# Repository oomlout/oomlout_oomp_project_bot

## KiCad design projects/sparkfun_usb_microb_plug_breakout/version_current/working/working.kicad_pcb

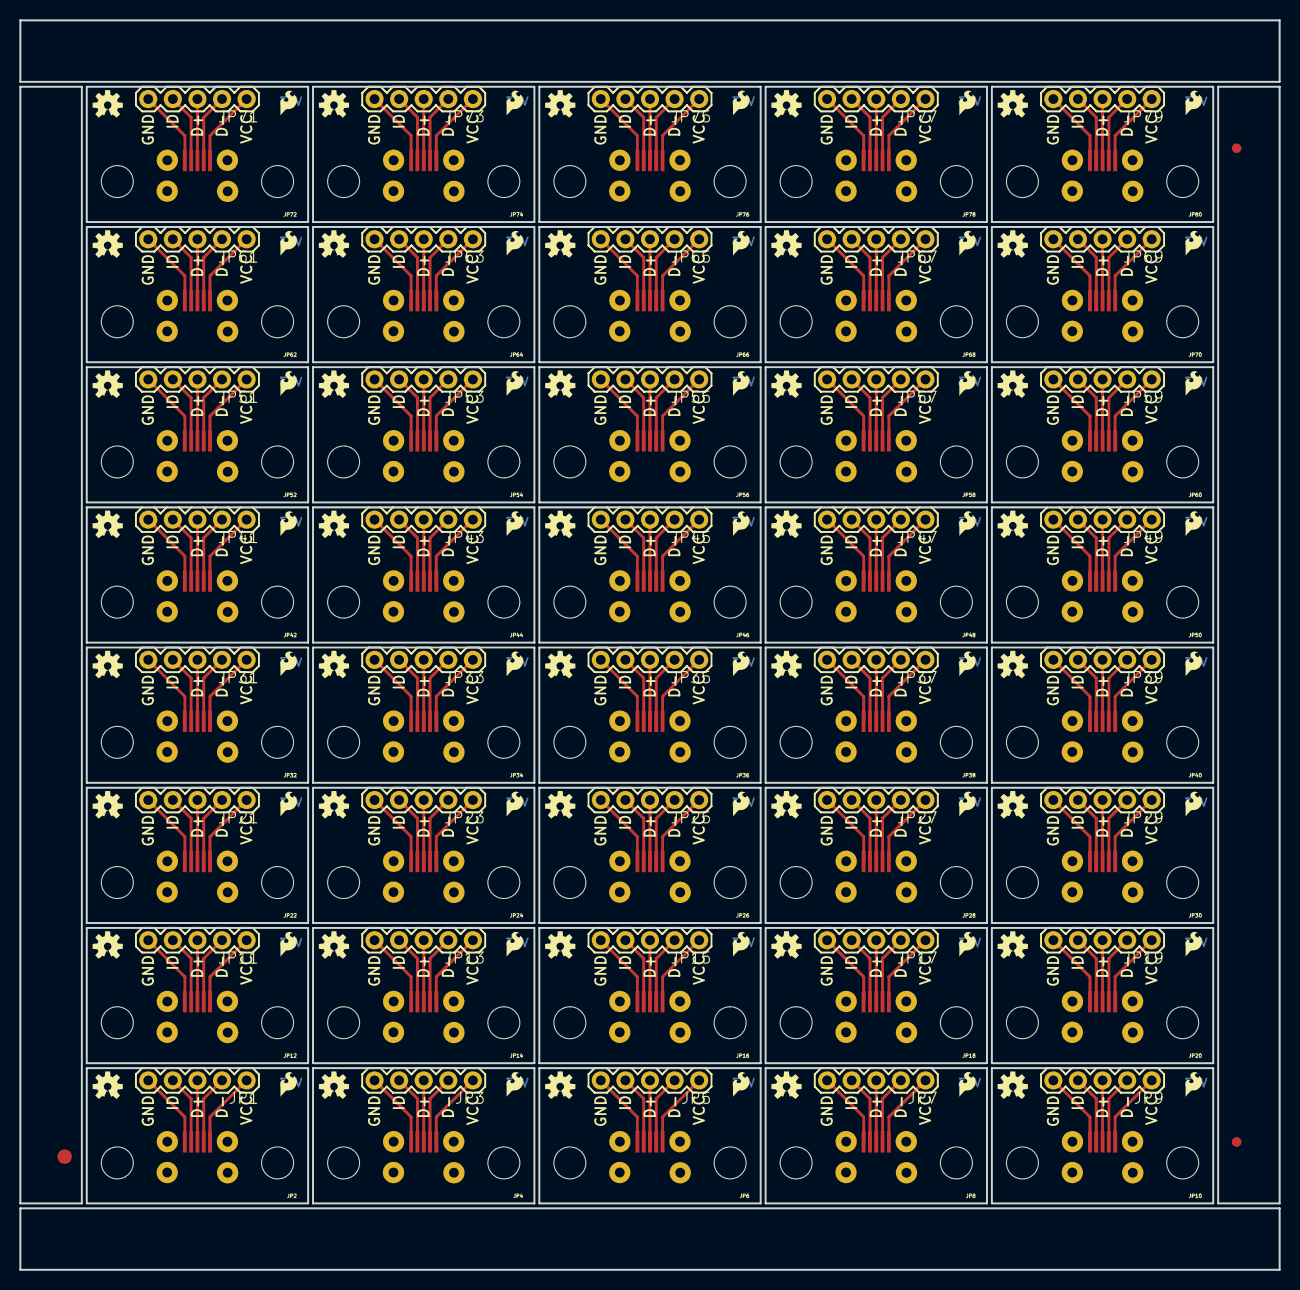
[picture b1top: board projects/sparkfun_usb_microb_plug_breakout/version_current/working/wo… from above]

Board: 2 copper layers, 130.0 x 129.0 mm, 163 parts (0 on the bottom side), 200 nets.

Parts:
E$1: FIDUCIAL-1.5X3
E$4, E$5: FIDUCIAL-1X2
JP1, JP3, JP5, JP7, JP9, JP11, JP13, JP15, JP17, JP19, JP21, JP23, JP25, JP27, JP29, JP31, JP33, JP35, JP37, JP39, JP41, JP43, JP45, JP47, JP49, JP51, JP53, JP55, JP57, JP59, JP61, JP63, JP65, JP67, JP69, JP71, JP73, JP75, JP77, JP79: 1X05
JP2, JP4, JP6, JP8, JP10, JP12, JP14, JP16, JP18, JP20, JP22, JP24, JP26, JP28, JP30, JP32, JP34, JP36, JP38, JP40, JP42, JP44, JP46, JP48, JP50, JP52, JP54, JP56, JP58, JP60, JP62, JP64, JP66, JP68, JP70, JP72, JP74, JP76, JP78, JP80: USB Micro B Plug; MICRO-B-SMT
LOGO1, LOGO3, LOGO5, LOGO7, LOGO9, LOGO11, LOGO13, LOGO15, LOGO17, LOGO19, LOGO21, LOGO23, LOGO25, LOGO27, LOGO29, LOGO31, LOGO33, LOGO35, LOGO37, LOGO39, LOGO41, LOGO43, LOGO45, LOGO47, LOGO49, LOGO51, LOGO53, LOGO55, LOGO57, LOGO59, LOGO61, LOGO63, LOGO65, LOGO67, LOGO69, LOGO71, LOGO73, LOGO75, LOGO77, LOGO79: OSHW-LOGOS; OSHW-LOGO-S
LOGO2, LOGO4, LOGO6, LOGO8, LOGO10, LOGO12, LOGO14, LOGO16, LOGO18, LOGO20, LOGO22, LOGO24, LOGO26, LOGO28, LOGO30, LOGO32, LOGO34, LOGO36, LOGO38, LOGO40, LOGO42, LOGO44, LOGO46, LOGO48, LOGO50, LOGO52, LOGO54, LOGO56, LOGO58, LOGO60, LOGO62, LOGO64, LOGO66, LOGO68, LOGO70, LOGO72, LOGO74, LOGO76, LOGO78, LOGO80: SFE_LOGO_FLAME.1_INCH; SFE_LOGO_FLAME_.1

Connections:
unnamed: JP1.1, JP2.1
unnamed: JP1.2, JP2.2
unnamed: JP1.3, JP2.3
unnamed: JP1.4, JP2.4
unnamed: JP1.5, JP2.5
unnamed: JP3.1, JP4.1
unnamed: JP3.2, JP4.2
unnamed: JP3.3, JP4.3
unnamed: JP3.4, JP4.4
unnamed: JP3.5, JP4.5
unnamed: JP5.1, JP6.1
unnamed: JP5.2, JP6.2
unnamed: JP5.3, JP6.3
unnamed: JP5.4, JP6.4
unnamed: JP5.5, JP6.5
unnamed: JP7.1, JP8.1
unnamed: JP7.2, JP8.2
unnamed: JP7.3, JP8.3
unnamed: JP7.4, JP8.4
unnamed: JP7.5, JP8.5
unnamed: JP9.1, JP10.1
unnamed: JP9.2, JP10.2
unnamed: JP9.3, JP10.3
unnamed: JP9.4, JP10.4
unnamed: JP9.5, JP10.5
unnamed: JP11.1, JP12.1
unnamed: JP11.2, JP12.2
unnamed: JP11.3, JP12.3
unnamed: JP11.4, JP12.4
unnamed: JP11.5, JP12.5
unnamed: JP13.1, JP14.1
unnamed: JP13.2, JP14.2
unnamed: JP13.3, JP14.3
unnamed: JP13.4, JP14.4
unnamed: JP13.5, JP14.5
unnamed: JP15.1, JP16.1
unnamed: JP15.2, JP16.2
unnamed: JP15.3, JP16.3
unnamed: JP15.4, JP16.4
unnamed: JP15.5, JP16.5
unnamed: JP17.1, JP18.1
unnamed: JP17.2, JP18.2
unnamed: JP17.3, JP18.3
unnamed: JP17.4, JP18.4
unnamed: JP17.5, JP18.5
unnamed: JP19.1, JP20.1
unnamed: JP19.2, JP20.2
unnamed: JP19.3, JP20.3
unnamed: JP19.4, JP20.4
unnamed: JP19.5, JP20.5
unnamed: JP21.1, JP22.1
unnamed: JP21.2, JP22.2
unnamed: JP21.3, JP22.3
unnamed: JP21.4, JP22.4
unnamed: JP21.5, JP22.5
unnamed: JP23.1, JP24.1
unnamed: JP23.2, JP24.2
unnamed: JP23.3, JP24.3
unnamed: JP23.4, JP24.4
unnamed: JP23.5, JP24.5
unnamed: JP25.1, JP26.1
unnamed: JP25.2, JP26.2
unnamed: JP25.3, JP26.3
unnamed: JP25.4, JP26.4
unnamed: JP25.5, JP26.5
unnamed: JP27.1, JP28.1
unnamed: JP27.2, JP28.2
unnamed: JP27.3, JP28.3
unnamed: JP27.4, JP28.4
unnamed: JP27.5, JP28.5
unnamed: JP29.1, JP30.1
unnamed: JP29.2, JP30.2
unnamed: JP29.3, JP30.3
unnamed: JP29.4, JP30.4
unnamed: JP29.5, JP30.5
unnamed: JP31.1, JP32.1
unnamed: JP31.2, JP32.2
unnamed: JP31.3, JP32.3
unnamed: JP31.4, JP32.4
unnamed: JP31.5, JP32.5
unnamed: JP33.1, JP34.1
unnamed: JP33.2, JP34.2
unnamed: JP33.3, JP34.3
unnamed: JP33.4, JP34.4
unnamed: JP33.5, JP34.5
unnamed: JP35.1, JP36.1
unnamed: JP35.2, JP36.2
unnamed: JP35.3, JP36.3
unnamed: JP35.4, JP36.4
unnamed: JP35.5, JP36.5
unnamed: JP37.1, JP38.1
unnamed: JP37.2, JP38.2
unnamed: JP37.3, JP38.3
unnamed: JP37.4, JP38.4
unnamed: JP37.5, JP38.5
unnamed: JP39.1, JP40.1
unnamed: JP39.2, JP40.2
unnamed: JP39.3, JP40.3
unnamed: JP39.4, JP40.4
unnamed: JP39.5, JP40.5
unnamed: JP41.1, JP42.1
unnamed: JP41.2, JP42.2
unnamed: JP41.3, JP42.3
unnamed: JP41.4, JP42.4
unnamed: JP41.5, JP42.5
unnamed: JP43.1, JP44.1
unnamed: JP43.2, JP44.2
unnamed: JP43.3, JP44.3
unnamed: JP43.4, JP44.4
unnamed: JP43.5, JP44.5
unnamed: JP45.1, JP46.1
unnamed: JP45.2, JP46.2
unnamed: JP45.3, JP46.3
unnamed: JP45.4, JP46.4
unnamed: JP45.5, JP46.5
unnamed: JP47.1, JP48.1
unnamed: JP47.2, JP48.2
unnamed: JP47.3, JP48.3
unnamed: JP47.4, JP48.4
unnamed: JP47.5, JP48.5
unnamed: JP49.1, JP50.1
unnamed: JP49.2, JP50.2
unnamed: JP49.3, JP50.3
unnamed: JP49.4, JP50.4
unnamed: JP49.5, JP50.5
unnamed: JP51.1, JP52.1
unnamed: JP51.2, JP52.2
unnamed: JP51.3, JP52.3
unnamed: JP51.4, JP52.4
unnamed: JP51.5, JP52.5
unnamed: JP53.1, JP54.1
unnamed: JP53.2, JP54.2
unnamed: JP53.3, JP54.3
unnamed: JP53.4, JP54.4
unnamed: JP53.5, JP54.5
unnamed: JP55.1, JP56.1
unnamed: JP55.2, JP56.2
unnamed: JP55.3, JP56.3
unnamed: JP55.4, JP56.4
unnamed: JP55.5, JP56.5
unnamed: JP57.1, JP58.1
unnamed: JP57.2, JP58.2
unnamed: JP57.3, JP58.3
unnamed: JP57.4, JP58.4
unnamed: JP57.5, JP58.5
unnamed: JP59.1, JP60.1
unnamed: JP59.2, JP60.2
unnamed: JP59.3, JP60.3
unnamed: JP59.4, JP60.4
unnamed: JP59.5, JP60.5
unnamed: JP61.1, JP62.1
unnamed: JP61.2, JP62.2
unnamed: JP61.3, JP62.3
unnamed: JP61.4, JP62.4
unnamed: JP61.5, JP62.5
unnamed: JP63.1, JP64.1
unnamed: JP63.2, JP64.2
unnamed: JP63.3, JP64.3
unnamed: JP63.4, JP64.4
unnamed: JP63.5, JP64.5
unnamed: JP65.1, JP66.1
unnamed: JP65.2, JP66.2
unnamed: JP65.3, JP66.3
unnamed: JP65.4, JP66.4
unnamed: JP65.5, JP66.5
unnamed: JP67.1, JP68.1
unnamed: JP67.2, JP68.2
unnamed: JP67.3, JP68.3
unnamed: JP67.4, JP68.4
unnamed: JP67.5, JP68.5
unnamed: JP69.1, JP70.1
unnamed: JP69.2, JP70.2
unnamed: JP69.3, JP70.3
unnamed: JP69.4, JP70.4
unnamed: JP69.5, JP70.5
unnamed: JP71.1, JP72.1
unnamed: JP71.2, JP72.2
unnamed: JP71.3, JP72.3
unnamed: JP71.4, JP72.4
unnamed: JP71.5, JP72.5
unnamed: JP73.1, JP74.1
unnamed: JP73.2, JP74.2
unnamed: JP73.3, JP74.3
unnamed: JP73.4, JP74.4
unnamed: JP73.5, JP74.5
unnamed: JP75.1, JP76.1
unnamed: JP75.2, JP76.2
unnamed: JP75.3, JP76.3
unnamed: JP75.4, JP76.4
unnamed: JP75.5, JP76.5
unnamed: JP77.1, JP78.1
unnamed: JP77.2, JP78.2
unnamed: JP77.3, JP78.3
unnamed: JP77.4, JP78.4
unnamed: JP77.5, JP78.5
unnamed: JP79.1, JP80.1
unnamed: JP79.2, JP80.2
unnamed: JP79.3, JP80.3
unnamed: JP79.4, JP80.4
unnamed: JP79.5, JP80.5

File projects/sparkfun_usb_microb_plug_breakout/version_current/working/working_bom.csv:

"Id";"Designator";"Footprint";"Quantity";"Designation";"Supplier and ref";
1;"LOGO5,LOGO25,LOGO69,LOGO53,LOGO77,LOGO17,LOGO79,LOGO11,LOGO43,LOGO55,LOGO71,LOGO61,LOGO13,LOGO33,LOGO21,LOGO3,LOGO63,LOGO15,LOGO35,LOGO45,LOGO41,LOGO9,LOGO59,LOGO51,LOGO49,LOGO67,LOGO73,LOGO47,LOGO19,LOGO57,LOGO39,LOGO7,LOGO29,LOGO23,LOGO75,LOGO37,LOGO1,LOGO27,LOGO31,LOGO65";"OSHW-LOGO-S";40;"OSHW-LOGOS";;;
2;"LOGO74,LOGO68,LOGO24,LOGO14,LOGO76,LOGO46,LOGO54,LOGO42,LOGO30,LOGO50,LOGO38,LOGO64,LOGO62,LOGO12,LOGO70,LOGO60,LOGO48,LOGO36,LOGO22,LOGO78,LOGO16,LOGO52,LOGO2,LOGO6,LOGO80,LOGO32,LOGO18,LOGO8,LOGO56,LOGO72,LOGO66,LOGO28,LOGO40,LOGO44,LOGO10,LOGO20,LOGO4,LOGO58,LOGO34,LOGO26";"SFE_LOGO_FLAME_.1";40;"SFE_LOGO_FLAME.1_INCH";;;
3;"JP75,JP55,JP21,JP9,JP65,JP59,JP79,JP19,JP25,JP51,JP29,JP57,JP31,JP39,JP7,JP35,JP69,JP49,JP41,JP73,JP67,JP33,JP15,JP53,JP27,JP5,JP13,JP43,JP3,JP11,JP63,JP17,JP1,JP37,JP45,JP47,JP71,JP77,JP23,JP61";"1X05";40;"";;;
4;"JP68,JP64,JP50,JP72,JP54,JP58,JP36,JP14,JP16,JP38,JP20,JP24,JP4,JP46,JP48,JP56,JP40,JP2,JP30,JP26,JP52,JP44,JP22,JP18,JP10,JP66,JP76,JP8,JP12,JP60,JP34,JP70,JP28,JP6,JP62,JP32,JP78,JP74,JP42,JP80";"MICRO-B-SMT";40;"USB Micro B Plug";;;
5;"E$4,E$5";"FIDUCIAL-1X2";2;"";;;
6;"E$1";"FIDUCIAL-1.5X3";1;"";;;

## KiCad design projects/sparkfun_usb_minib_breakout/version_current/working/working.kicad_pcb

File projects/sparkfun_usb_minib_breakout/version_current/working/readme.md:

# USB_miniB_Breakout by sparkfun  
This is a harvested standardized copy of a project from github.  
The original project can be found at:  
https://github.com/sparkfun/USB_miniB_Breakout  
Please consult that link for additional, details, files, and license information.  
Note: It was auto harvested and if the original repo had more than one board file or anything out of the ordinary the files here are likely not representative.

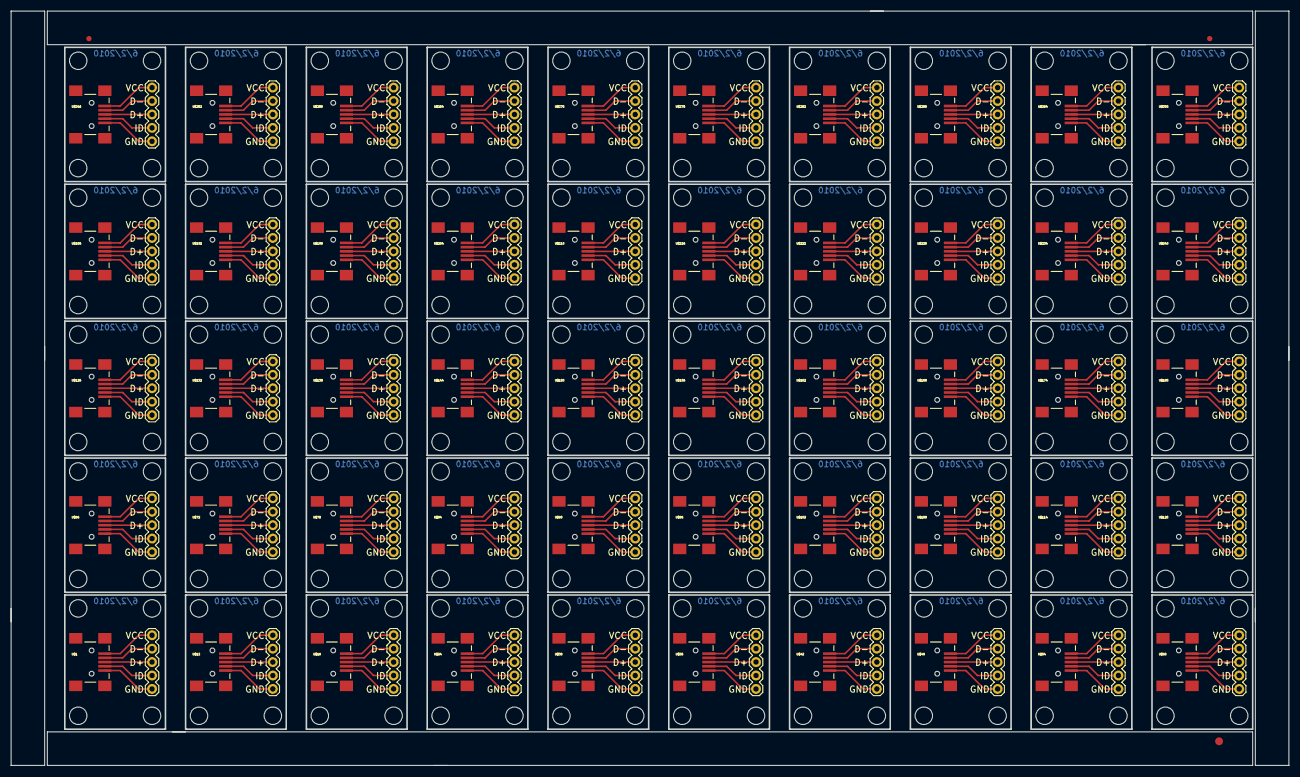
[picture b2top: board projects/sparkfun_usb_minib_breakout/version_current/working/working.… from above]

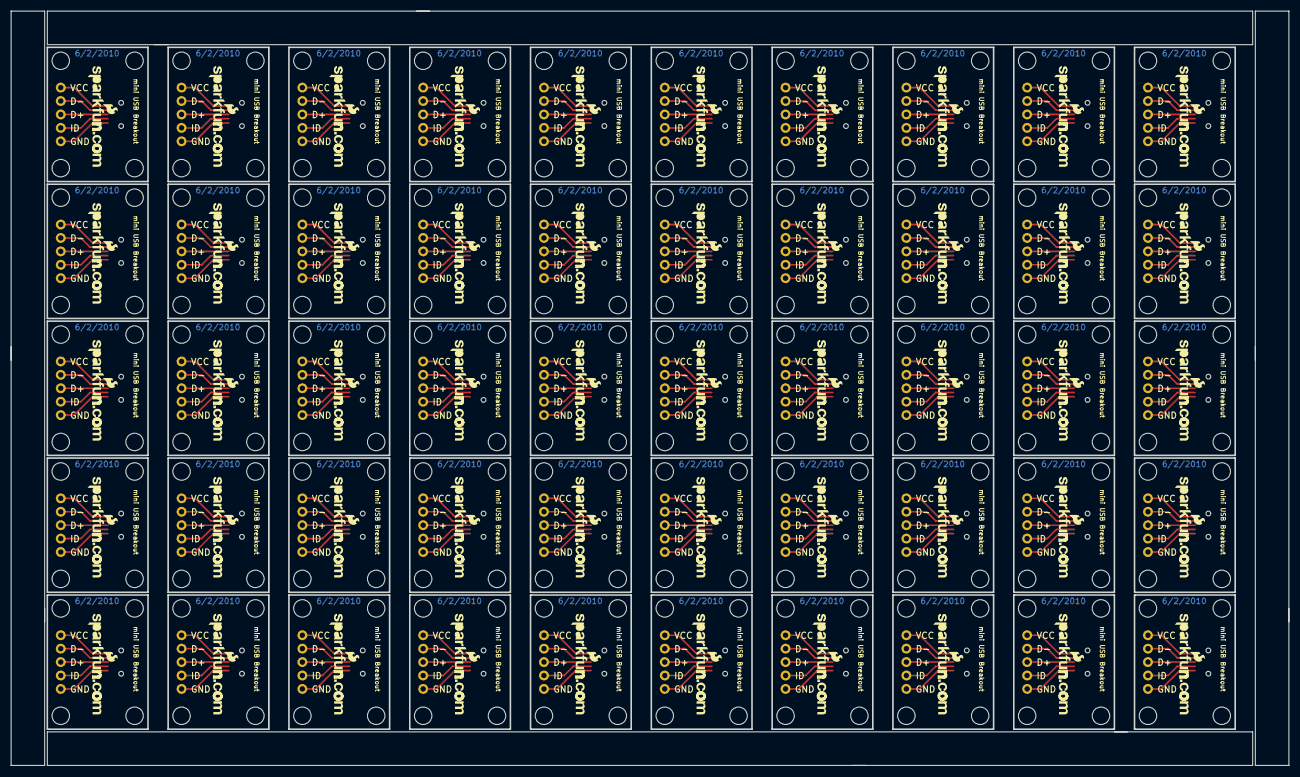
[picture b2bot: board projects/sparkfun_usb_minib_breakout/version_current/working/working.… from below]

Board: 2 copper layers, 241.8 x 142.7 mm, 353 parts (50 on the bottom side), 250 nets.

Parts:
E$1: FIDUCIAL-1.5X3
E$7, E$8: FIDUCIAL-1X2
JP1, JP2, JP3, JP4, JP5, JP6, JP7, JP8, JP9, JP10, JP11, JP12, JP13, JP14, JP15, JP16, JP17, JP18, JP19, JP20, JP21, JP22, JP23, JP24, JP25, JP26, JP27, JP28, JP29, JP30, JP31, JP32, JP33, JP34, JP35, JP36, JP37, JP38, JP39, JP40, JP41, JP42, JP43, JP44, JP45, JP46, JP47, JP48, JP49, JP50: 1X05
U$1, U$12, U$18, U$24, U$30, U$36, U$42, U$48, U$54, U$60, U$66, U$72, U$78, U$84, U$90, U$96, U$102, U$108, U$114, U$120, U$126, U$132, U$138, U$144, U$150, U$156, U$162, U$168, U$174, U$180, U$186, U$192, U$198, U$204, U$210, U$216, U$222, U$228, U$234, U$240, U$246, U$252, U$258, U$264, U$270, U$276, U$282, U$288, U$294, U$300: USB-MINIB-5PIN; USB-MINIB
U$2, U$3, U$4, U$5, U$7, U$8, U$9, U$10, U$13, U$14, U$15, U$16, U$19, U$20, U$21, U$22, U$25, U$26, U$27, U$28, U$31, U$32, U$33, U$34, U$37, U$38, U$39, U$40, U$43, U$44, U$45, U$46, U$49, U$50, U$51, U$52, U$55, U$56, U$57, U$58, U$61, U$62, U$63, U$64, U$67, U$68, U$69, U$70, U$73, U$74, U$75, U$76, U$79, U$80, U$81, U$82, U$85, U$86, U$87, U$88, U$91, U$92, U$93, U$94, U$97, U$98, U$99, U$100, U$103, U$104, U$105, U$106, U$109, U$110, U$111, U$112, U$115, U$116, U$117, U$118, U$121, U$122, U$123, U$124, U$127, U$128, U$129, U$130, U$133, U$134, U$135, U$136, U$139, U$140, U$141, U$142, U$145, U$146, U$147, U$148, U$151, U$152, U$153, U$154, U$157, U$158, U$159, U$160, U$163, U$164, U$165, U$166, U$169, U$170, U$171, U$172, U$175, U$176, U$177, U$178, U$181, U$182, U$183, U$184, U$187, U$188, U$189, U$190, U$193, U$194, U$195, U$196, U$199, U$200, U$201, U$202, U$205, U$206, U$207, U$208, U$211, U$212, U$213, U$214, U$217, U$218, U$219, U$220, U$223, U$224, U$225, U$226, U$229, U$230, U$231, U$232, U$235, U$236, U$237, U$238, U$241, U$242, U$243, U$244, U$247, U$248, U$249, U$250, U$253, U$254, U$255, U$256, U$259, U$260, U$261, U$262, U$265, U$266, U$267, U$268, U$271, U$272, U$273, U$274, U$277, U$278, U$279, U$280, U$283, U$284, U$285, U$286, U$289, U$290, U$291, U$292, U$295, U$296, U$297, U$298: STAND-OFF
U$6, U$11, U$17, U$23, U$29, U$35, U$41, U$47, U$53, U$59, U$65, U$71, U$77, U$83, U$89, U$95, U$101, U$107, U$113, U$119, U$125, U$131, U$137, U$143, U$149, U$155, U$161, U$167, U$173, U$179, U$185, U$191, U$197, U$203, U$209, U$215, U$221, U$227, U$233, U$239, U$245, U$251, U$257, U$263, U$269, U$275, U$281, U$287, U$293, U$299: LOGO-SFENEW; SFE-NEW-WEBLOGO

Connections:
GND: JP1.5, U$1.GND
GND1: JP2.5, U$12.GND
GND2: JP3.5, U$18.GND
GND3: JP4.5, U$24.GND
GND4: JP5.5, U$30.GND
GND5: JP6.5, U$36.GND
GND6: JP7.5, U$42.GND
GND7: JP8.5, U$48.GND
GND8: JP9.5, U$54.GND
GND9: JP10.5, U$60.GND
GND10: JP11.5, U$66.GND
GND11: JP12.5, U$72.GND
GND12: JP13.5, U$78.GND
GND13: JP14.5, U$84.GND
GND14: JP15.5, U$90.GND
GND15: JP16.5, U$96.GND
GND16: JP17.5, U$102.GND
GND17: JP18.5, U$108.GND
GND18: JP19.5, U$114.GND
GND19: JP20.5, U$120.GND
GND20: JP21.5, U$126.GND
GND21: JP22.5, U$132.GND
GND22: JP23.5, U$138.GND
GND23: JP24.5, U$144.GND
GND24: JP25.5, U$150.GND
GND25: JP26.5, U$156.GND
GND26: JP27.5, U$162.GND
GND27: JP28.5, U$168.GND
GND28: JP29.5, U$174.GND
GND29: JP30.5, U$180.GND
GND30: JP31.5, U$186.GND
GND31: JP32.5, U$192.GND
GND32: JP33.5, U$198.GND
GND33: JP34.5, U$204.GND
GND34: JP35.5, U$210.GND
GND35: JP36.5, U$216.GND
GND36: JP37.5, U$222.GND
GND37: JP38.5, U$228.GND
GND38: JP39.5, U$234.GND
GND39: JP40.5, U$240.GND
GND40: JP41.5, U$246.GND
GND41: JP42.5, U$252.GND
GND42: JP43.5, U$258.GND
GND43: JP44.5, U$264.GND
GND44: JP45.5, U$270.GND
GND45: JP46.5, U$276.GND
GND46: JP47.5, U$282.GND
GND47: JP48.5, U$288.GND
GND48: JP49.5, U$294.GND
GND49: JP50.5, U$300.GND
unnamed: JP1.2, U$1.D-
unnamed: JP1.1, U$1.VBUS
unnamed: JP1.3, U$1.D+
unnamed: JP2.2, U$12.D-
unnamed: JP1.4, U$1.ID
unnamed: JP2.1, U$12.VBUS
unnamed: JP2.3, U$12.D+
unnamed: JP2.4, U$12.ID
unnamed: JP3.2, U$18.D-
unnamed: JP3.1, U$18.VBUS
unnamed: JP3.3, U$18.D+
unnamed: JP3.4, U$18.ID
unnamed: JP4.2, U$24.D-
unnamed: JP4.1, U$24.VBUS
unnamed: JP4.3, U$24.D+
unnamed: JP4.4, U$24.ID
unnamed: JP5.2, U$30.D-
unnamed: JP5.1, U$30.VBUS
unnamed: JP5.3, U$30.D+
unnamed: JP5.4, U$30.ID
unnamed: JP6.2, U$36.D-
unnamed: JP6.1, U$36.VBUS
unnamed: JP6.3, U$36.D+
unnamed: JP6.4, U$36.ID
unnamed: JP7.2, U$42.D-
unnamed: JP7.1, U$42.VBUS
unnamed: JP7.3, U$42.D+
unnamed: JP7.4, U$42.ID
unnamed: JP8.2, U$48.D-
unnamed: JP8.1, U$48.VBUS
unnamed: JP8.3, U$48.D+
unnamed: JP8.4, U$48.ID
unnamed: JP9.2, U$54.D-
unnamed: JP9.1, U$54.VBUS
unnamed: JP9.3, U$54.D+
unnamed: JP9.4, U$54.ID
unnamed: JP10.2, U$60.D-
unnamed: JP10.1, U$60.VBUS
unnamed: JP10.3, U$60.D+
unnamed: JP10.4, U$60.ID
unnamed: JP11.2, U$66.D-
unnamed: JP11.1, U$66.VBUS
unnamed: JP11.3, U$66.D+
unnamed: JP11.4, U$66.ID
unnamed: JP12.2, U$72.D-
unnamed: JP12.1, U$72.VBUS
unnamed: JP12.3, U$72.D+
unnamed: JP12.4, U$72.ID
unnamed: JP13.2, U$78.D-
unnamed: JP13.1, U$78.VBUS
unnamed: JP13.3, U$78.D+
unnamed: JP13.4, U$78.ID
unnamed: JP14.2, U$84.D-
unnamed: JP14.1, U$84.VBUS
unnamed: JP14.3, U$84.D+
unnamed: JP14.4, U$84.ID
unnamed: JP15.2, U$90.D-
unnamed: JP15.1, U$90.VBUS
unnamed: JP15.3, U$90.D+
unnamed: JP15.4, U$90.ID
unnamed: JP16.2, U$96.D-
unnamed: JP16.1, U$96.VBUS
unnamed: JP16.3, U$96.D+
unnamed: JP16.4, U$96.ID
unnamed: JP17.2, U$102.D-
unnamed: JP17.1, U$102.VBUS
unnamed: JP17.3, U$102.D+
unnamed: JP17.4, U$102.ID
unnamed: JP18.2, U$108.D-
unnamed: JP18.1, U$108.VBUS
unnamed: JP18.3, U$108.D+
unnamed: JP18.4, U$108.ID
unnamed: JP19.2, U$114.D-
unnamed: JP19.1, U$114.VBUS
unnamed: JP19.3, U$114.D+
unnamed: JP19.4, U$114.ID
unnamed: JP20.2, U$120.D-
unnamed: JP20.1, U$120.VBUS
unnamed: JP20.3, U$120.D+
unnamed: JP20.4, U$120.ID
unnamed: JP21.2, U$126.D-
unnamed: JP21.1, U$126.VBUS
unnamed: JP21.3, U$126.D+
unnamed: JP21.4, U$126.ID
unnamed: JP22.2, U$132.D-
unnamed: JP22.1, U$132.VBUS
unnamed: JP22.3, U$132.D+
unnamed: JP22.4, U$132.ID
unnamed: JP23.2, U$138.D-
unnamed: JP23.1, U$138.VBUS
unnamed: JP23.3, U$138.D+
unnamed: JP23.4, U$138.ID
unnamed: JP24.2, U$144.D-
unnamed: JP24.1, U$144.VBUS
unnamed: JP24.3, U$144.D+
unnamed: JP24.4, U$144.ID
unnamed: JP25.2, U$150.D-
unnamed: JP25.1, U$150.VBUS
unnamed: JP25.3, U$150.D+
unnamed: JP25.4, U$150.ID
unnamed: JP26.2, U$156.D-
unnamed: JP26.1, U$156.VBUS
unnamed: JP26.3, U$156.D+
unnamed: JP26.4, U$156.ID
unnamed: JP27.2, U$162.D-
unnamed: JP27.1, U$162.VBUS
unnamed: JP27.3, U$162.D+
unnamed: JP27.4, U$162.ID
unnamed: JP28.2, U$168.D-
unnamed: JP28.1, U$168.VBUS
unnamed: JP28.3, U$168.D+
unnamed: JP28.4, U$168.ID
unnamed: JP29.2, U$174.D-
unnamed: JP29.1, U$174.VBUS
unnamed: JP29.3, U$174.D+
unnamed: JP29.4, U$174.ID
unnamed: JP30.2, U$180.D-
unnamed: JP30.1, U$180.VBUS
unnamed: JP30.3, U$180.D+
unnamed: JP30.4, U$180.ID
unnamed: JP31.2, U$186.D-
unnamed: JP31.1, U$186.VBUS
unnamed: JP31.3, U$186.D+
unnamed: JP31.4, U$186.ID
unnamed: JP32.2, U$192.D-
unnamed: JP32.1, U$192.VBUS
unnamed: JP32.3, U$192.D+
unnamed: JP32.4, U$192.ID
unnamed: JP33.2, U$198.D-
unnamed: JP33.1, U$198.VBUS
unnamed: JP33.3, U$198.D+
unnamed: JP33.4, U$198.ID
unnamed: JP34.2, U$204.D-
unnamed: JP34.1, U$204.VBUS
unnamed: JP34.3, U$204.D+
unnamed: JP34.4, U$204.ID
unnamed: JP35.2, U$210.D-
unnamed: JP35.1, U$210.VBUS
unnamed: JP35.3, U$210.D+
unnamed: JP35.4, U$210.ID
unnamed: JP36.2, U$216.D-
unnamed: JP36.1, U$216.VBUS
unnamed: JP36.3, U$216.D+
unnamed: JP36.4, U$216.ID
unnamed: JP37.2, U$222.D-
unnamed: JP37.1, U$222.VBUS
unnamed: JP37.3, U$222.D+
unnamed: JP37.4, U$222.ID
unnamed: JP38.2, U$228.D-
unnamed: JP38.1, U$228.VBUS
unnamed: JP38.3, U$228.D+
unnamed: JP38.4, U$228.ID
unnamed: JP39.2, U$234.D-
unnamed: JP39.1, U$234.VBUS
unnamed: JP39.3, U$234.D+
unnamed: JP39.4, U$234.ID
unnamed: JP40.2, U$240.D-
unnamed: JP40.1, U$240.VBUS
unnamed: JP40.3, U$240.D+
unnamed: JP40.4, U$240.ID
unnamed: JP41.2, U$246.D-
unnamed: JP41.1, U$246.VBUS
unnamed: JP41.3, U$246.D+
unnamed: JP41.4, U$246.ID
unnamed: JP42.2, U$252.D-
unnamed: JP42.1, U$252.VBUS
unnamed: JP42.3, U$252.D+
unnamed: JP42.4, U$252.ID
unnamed: JP43.2, U$258.D-
unnamed: JP43.1, U$258.VBUS
unnamed: JP43.3, U$258.D+
unnamed: JP43.4, U$258.ID
unnamed: JP44.2, U$264.D-
unnamed: JP44.1, U$264.VBUS
unnamed: JP44.3, U$264.D+
unnamed: JP44.4, U$264.ID
unnamed: JP45.2, U$270.D-
unnamed: JP45.1, U$270.VBUS
unnamed: JP45.3, U$270.D+
unnamed: JP45.4, U$270.ID
unnamed: JP46.2, U$276.D-
unnamed: JP46.1, U$276.VBUS
unnamed: JP46.3, U$276.D+
unnamed: JP46.4, U$276.ID
unnamed: JP47.2, U$282.D-
unnamed: JP47.1, U$282.VBUS
unnamed: JP47.3, U$282.D+
unnamed: JP47.4, U$282.ID
unnamed: JP48.2, U$288.D-
unnamed: JP48.1, U$288.VBUS
unnamed: JP48.3, U$288.D+
unnamed: JP48.4, U$288.ID
unnamed: JP49.2, U$294.D-
unnamed: JP49.1, U$294.VBUS
unnamed: JP49.3, U$294.D+
unnamed: JP49.4, U$294.ID
unnamed: JP50.2, U$300.D-
unnamed: JP50.1, U$300.VBUS
unnamed: JP50.3, U$300.D+
unnamed: JP50.4, U$300.ID

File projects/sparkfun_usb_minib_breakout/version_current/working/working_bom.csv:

"Id";"Designator";"Footprint";"Quantity";"Designation";"Supplier and ref";
1;"U$201,U$133,U$248,U$267,U$115,U$145,U$25,U$279,U$136,U$164,U$32,U$218,U$254,U$274,U$81,U$213,U$10,U$237,U$27,U$85,U$123,U$253,U$79,U$172,U$163,U$88,U$62,U$211,U$110,U$151,U$177,U$56,U$272,U$97,U$134,U$109,U$187,U$63,U$286,U$49,U$21,U$74,U$224,U$196,U$277,U$200,U$169,U$241,U$217,U$87,U$242,U$202,U$100,U$206,U$157,U$45,U$82,U$183,U$16,U$229,U$117,U$57,U$58,U$295,U$14,U$69,U$142,U$46,U$70,U$105,U$91,U$219,U$148,U$225,U$265,U$38,U$190,U$146,U$194,U$207,U$205,U$260,U$290,U$9,U$116,U$73,U$189,U$34,U$112,U$181,U$212,U$93,U$44,U$94,U$75,U$249,U$152,U$165,U$232,U$130,U$64,U$13,U$4,U$121,U$238,U$298,U$19,U$28,U$243,U$266,U$52,U$129,U$153,U$235,U$7,U$154,U$33,U$76,U$106,U$86,U$178,U$68,U$147,U$135,U$80,U$273,U$22,U$250,U$67,U$278,U$188,U$268,U$39,U$104,U$223,U$26,U$92,U$284,U$124,U$159,U$127,U$20,U$226,U$98,U$244,U$271,U$195,U$166,U$283,U$43,U$170,U$236,U$182,U$285,U$256,U$128,U$280,U$171,U$111,U$55,U$37,U$230,U$8,U$5,U$139,U$184,U$214,U$289,U$122,U$193,U$291,U$3,U$61,U$158,U$99,U$118,U$292,U$199,U$259,U$247,U$255,U$103,U$160,U$176,U$296,U$15,U$51,U$141,U$31,U$40,U$231,U$175,U$261,U$140,U$2,U$208,U$50,U$297,U$262,U$220";"STAND-OFF";200;"STAND-OFF";;;
2;"JP35,JP28,JP29,JP48,JP18,JP45,JP15,JP41,JP24,JP34,JP21,JP27,JP17,JP46,JP12,JP44,JP42,JP39,JP6,JP31,JP19,JP22,JP43,JP50,JP5,JP1,JP9,JP2,JP49,JP37,JP30,JP38,JP33,JP4,JP10,JP11,JP20,JP32,JP47,JP40,JP7,JP25,JP8,JP13,JP3,JP14,JP36,JP16,JP23,JP26";"1X05";50;"";;;
3;"U$222,U$294,U$66,U$288,U$252,U$300,U$150,U$36,U$210,U$48,U$18,U$78,U$246,U$90,U$24,U$234,U$126,U$108,U$186,U$156,U$168,U$228,U$84,U$216,U$138,U$270,U$120,U$264,U$96,U$162,U$30,U$276,U$204,U$282,U$144,U$114,U$1,U$12,U$174,U$258,U$180,U$72,U$60,U$192,U$42,U$102,U$54,U$198,U$240,U$132";"USB-MINIB";50;"USB-MINIB-5PIN";;;
4;"E$1";"FIDUCIAL-1.5X3";1;"";;;
5;"E$7,E$8";"FIDUCIAL-1X2";2;"";;;
6;"U$41,U$89,U$227,U$53,U$239,U$47,U$185,U$161,U$107,U$131,U$191,U$251,U$173,U$143,U$281,U$209,U$221,U$113,U$233,U$197,U$95,U$263,U$257,U$179,U$269,U$17,U$245,U$215,U$203,U$125,U$83,U$35,U$77,U$119,U$293,U$29,U$11,U$149,U$167,U$275,U$137,U$287,U$101,U$23,U$59,U$155,U$299,U$6,U$71,U$65";"SFE-NEW-WEBLOGO";50;"LOGO-SFENEW";;;

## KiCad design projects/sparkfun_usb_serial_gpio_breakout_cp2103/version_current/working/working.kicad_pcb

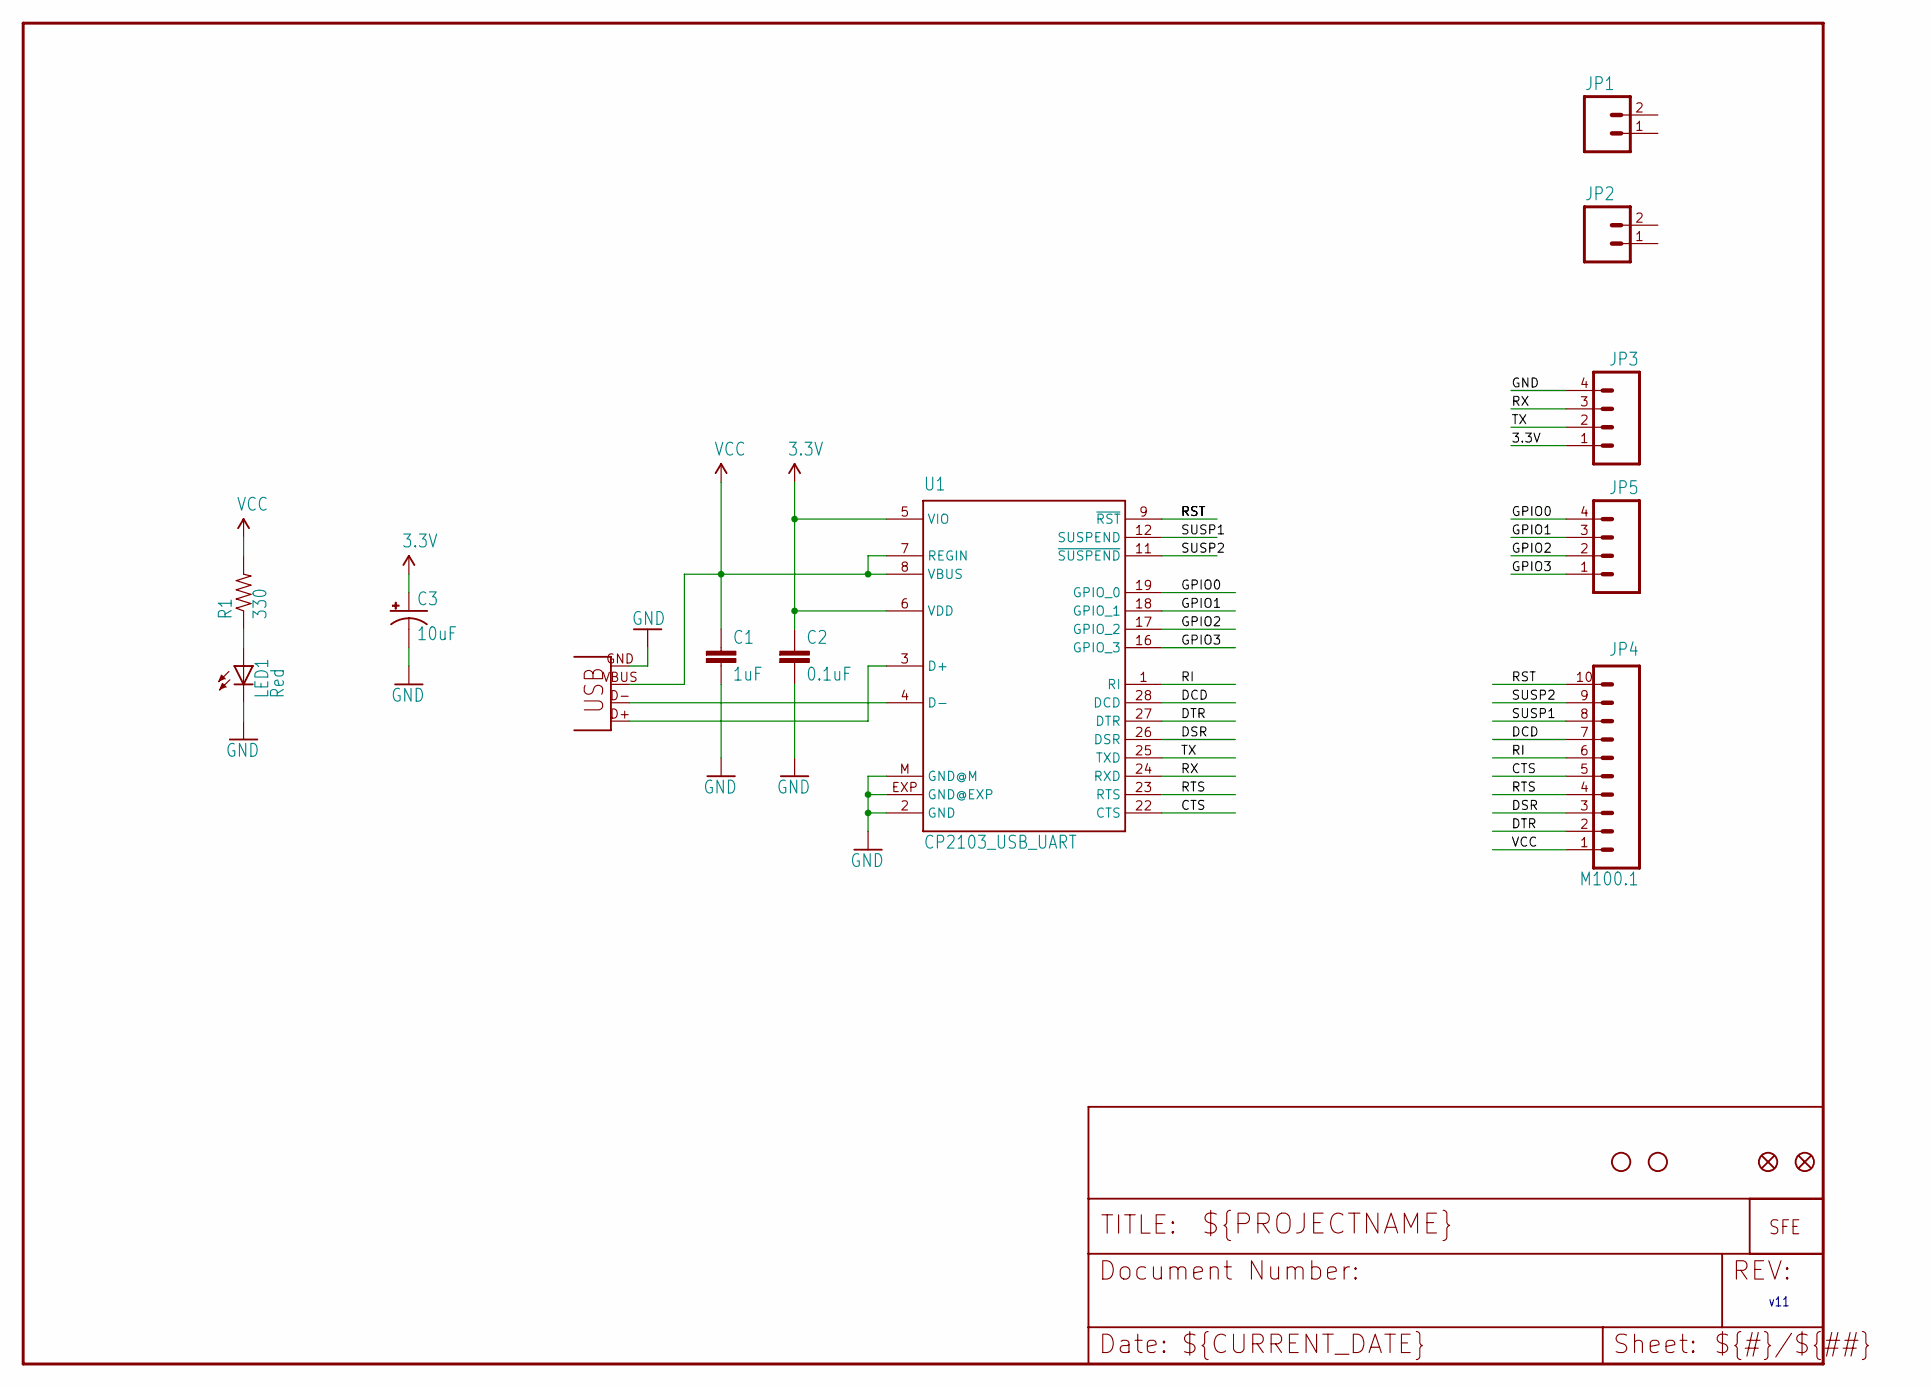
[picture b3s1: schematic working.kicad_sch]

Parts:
C1: 1uF; C0402
C2: 0.1uF; C0402
C3: 10uF; EIA3216
JP1, JP2: M02PTH; 1X02
JP3, JP5: M04PTH; 1X04
JP4: M100.1; 1X10
LED1: Red; LED-1206
R1: 330; C0402
U1: CP2103_USB_UART; MLP28
U$1: LOGO-SFENEW; SFE-NEW-WEBLOGO
U$2, U$3: FIDUCIAL1X2; FIDUCIAL-1X2
U$6, U$7: STAND-OFF
X1: USBPTH; USB-B-PTH

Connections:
3.3V: C2.1, C3.A (+), JP3.1, U1.5 (VIO), U1.6 (VDD)
CTS: JP4.5, U1.22 (CTS)
D+: U1.3 (D+), X1.D+
D-: U1.4 (D-), X1.D-
DCD: JP4.7, U1.28 (DCD)
DSR: JP4.3, U1.26 (DSR)
DTR: JP4.2, U1.27 (DTR)
GND: C1.2, C2.2, C3.C (-), JP3.4, LED1.C, U1.2 (GND), U1.EXP (GND@EXP), U1.M (GND@M), X1.GND
GPIO0: JP5.4, U1.19 (GPIO_0)
GPIO1: JP5.3, U1.18 (GPIO_1)
GPIO2: JP5.2, U1.17 (GPIO_2)
GPIO3: JP5.1, U1.16 (GPIO_3)
unnamed: LED1.A, R1.1
RI: JP4.6, U1.1 (RI)
RST: JP4.10, U1.9 (~RST)
RTS: JP4.4, U1.23 (RTS)
RX: JP3.3, U1.24 (RXD)
SUSP1: JP4.8, U1.12 (SUSPEND)
SUSP2: JP4.9, U1.11 (~SUSPEND)
TX: JP3.2, U1.25 (TXD)
VCC: C1.1, JP4.1, R1.2, U1.7 (REGIN), U1.8 (VBUS), X1.VBUS

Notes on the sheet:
v11

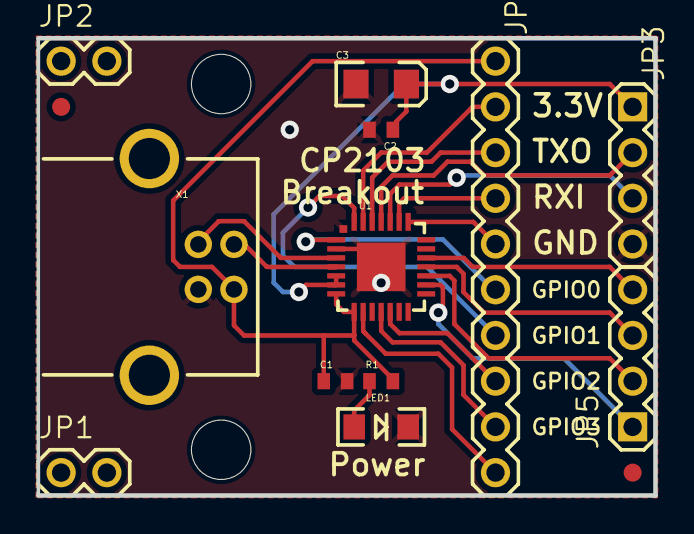
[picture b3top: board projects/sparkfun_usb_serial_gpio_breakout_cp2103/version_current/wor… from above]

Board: 2 copper layers, 34.3 x 25.4 mm, 17 parts (1 on the bottom side), 21 nets.

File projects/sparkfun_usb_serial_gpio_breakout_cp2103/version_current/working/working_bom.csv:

"Id";"Designator";"Footprint";"Quantity";"Designation";"Supplier and ref";
1;"U$3,U$2";"FIDUCIAL-1X2";2;"FIDUCIAL1X2";;;
2;"U$7,U$6";"STAND-OFF";2;"STAND-OFF";;;
3;"JP4";"1X10";1;"";;;
4;"C1";"C0402";1;"1uF";;;
5;"LED1";"LED-1206";1;"Red";;;
6;"X1";"USB-B-PTH";1;"USBPTH";;;
7;"U1";"MLP28";1;"CP2103";;;
8;"JP3,JP5";"1X04";2;"";;;
9;"JP2,JP1";"1X02";2;"";;;
10;"C2";"C0402";1;"0.1uF";;;
11;"R1";"C0402";1;"330";;;
12;"C3";"EIA3216";1;"10uF";;;
13;"U$1";"SFE-NEW-WEBLOGO";1;"LOGO-SFENEW";;;

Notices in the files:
projects/sparkfun_usb_microb_plug_breakout/version_current/working/working.kicad_sch:
https://creativecommons.org/licenses/by-sa/4.0
Released under the Creative Commons
projects/sparkfun_usb_type_a_female_breakout/version_current/working/working.kicad_sch:
http://creativecommons.org/licenses/by-sa/3.0
projects/sparkfun_voice_recorder_breakout_isd1932/version_current/working/working.kicad_sch:
Released under the Creative Commons Attribution Share-Alike 3.0 License
parts and their libraries:
Released under the Creative Commons Attribution Share-Alike 4.0 License
